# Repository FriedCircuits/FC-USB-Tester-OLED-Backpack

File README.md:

FC-USB-Tester-OLED-Backpack
===========================
This is the source code for the USB Tester OLED Backpack 

Which can be found at:
https://friedcircuits.us/tools/46

To compile this code you will need the following libraries:
===========================
Old Version

[Adafruit GFX](https://github.com/adafruit/Adafruit-GFX-Library)

[Adafruit SSD1306](https://github.com/adafruit/Adafruit_SSD1306)

2.0

Needs [UG8LIB] (https://github.com/olikraus/u8glib)

Both Versions

[TimerOne](https://github.com/PaulStoffregen/TimerOne)

[ClickButton](http://code.google.com/p/clickbutton/)

[Adafruit INA219](https://github.com/adafruit/Adafruit_INA219)

Download ZIP in each version folder for a working set with libraries and configuration of hardware SPI and display size

Use the new firmware version with the new Java app

https://github.com/FriedCircuits/FC-USB-Tester-Data-Logger-App

There may be a bug that shifts the display. We are working on a solution - Testing a new library for the display.

How to update firmware:

http://friedcircuits.us/docs/oled-backpack-how-to-update-firmware/

License: All source code and designs are released under 

Creative Commons NonCommercial-ShareAlike 

CC BY-NC-SA

Please contact me for commercial opportunities.

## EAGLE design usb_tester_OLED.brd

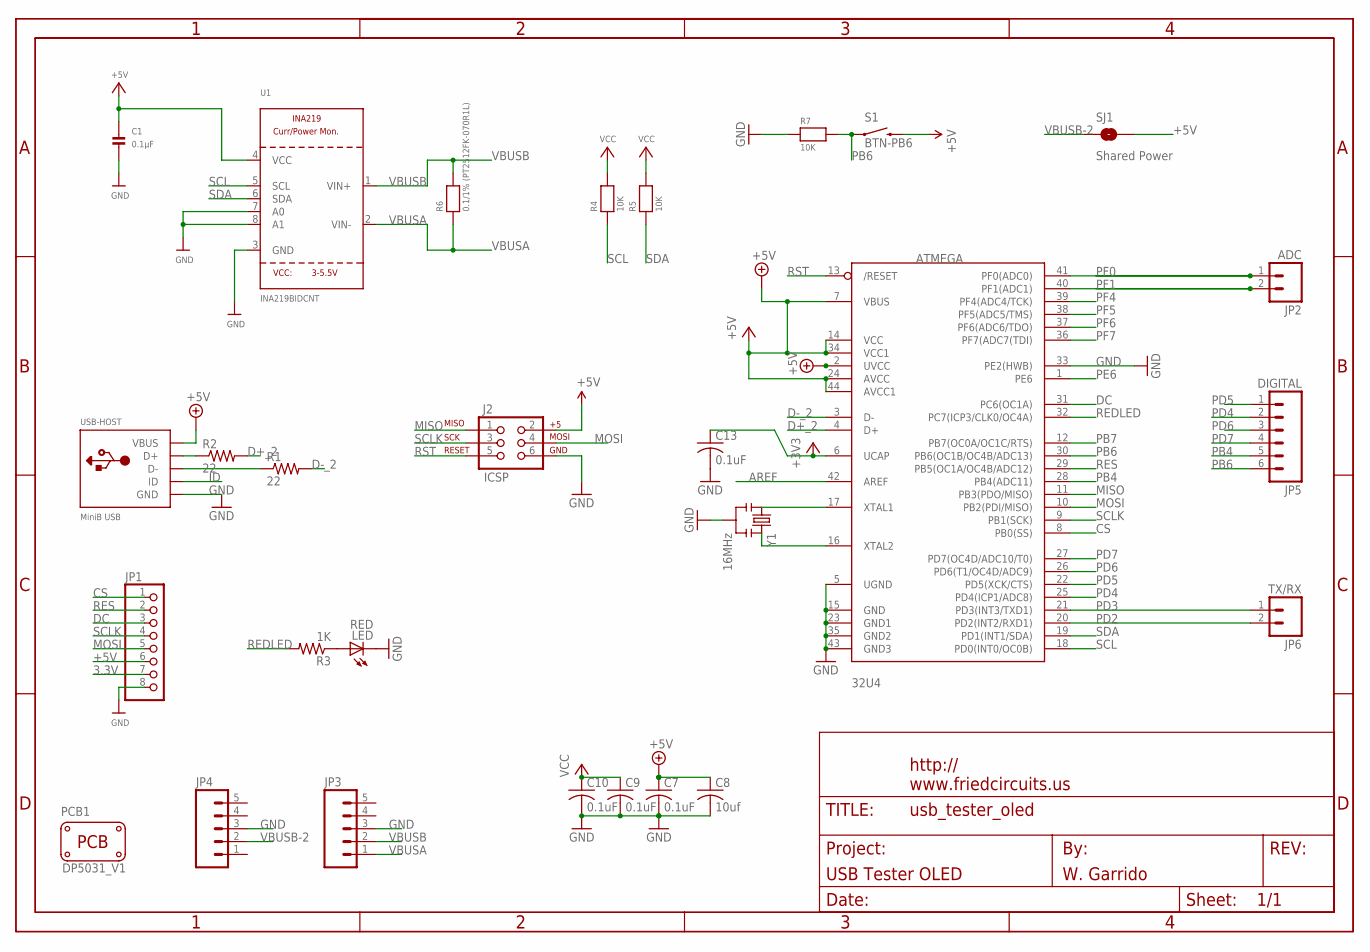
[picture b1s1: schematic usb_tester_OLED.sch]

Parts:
32U4: ATMEGA; TQFP44
C1: 0.1µF; 0805
C7, C9, C10, C13: 0.1uF; C0805K
C8: 10uf; C0805K
J2: ICSP; 2X3_LOCK
JP1: HEADER-1X876MIL; 1X08_ROUND_76
JP2: ADC; 1X02_LOCK
JP3, JP4: M05LOCK; 1X05_LOCK
JP5: DIGITAL; 1X06_LOCK
JP6: TX/RX; 1X02_LOCK
LED: RED; CHIPLED_0805
PCB1: PCB_DP_RECTANGLE-31X50; DP5031_V1
R1, R2: 22; R0805
R3: 1K; R0805
R4, R5, R7: 10K; 0805
R6: 0.1/1% (PT2512FK-070R1L); 2512
S1: BTN-PB6; TACTILE_SWITCH_SMD
SJ1: Shared Power; SJ_2S-TRACE
U1: INA219BIDCNT; SOT23-8
U$1: FRAME_DINA4_L; FC_CREDIT
USB-HOST: MiniB USB; USB-MINIB
Y1: 16MHz; RESONATOR-SMD

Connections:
3.3V: JP1.7
+3V3: 32U4.6 (UCAP), C13.1
+5V: 32U4.2 (UVCC), 32U4.7 (VBUS), 32U4.14 (VCC), 32U4.24 (AVCC), 32U4.34 (VCC1), 32U4.44 (AVCC1), C1.1, C7.1, C8.1, C9.1, C10.1, J2.2, JP1.6, R4.2, R5.2, S1.3 (2), SJ1.2, U1.4 (VCC), USB-HOST.VBUS
AREF: 32U4.42 (AREF)
CS: 32U4.8 (PB0(SS)), JP1.1
D+_2: 32U4.4 (D+), R2.2
D-_2: 32U4.3 (D-), R1.2
DC: 32U4.31 (PC6(OC1A)), JP1.3
GND: 32U4.5 (UGND), 32U4.15 (GND), 32U4.23 (GND1), 32U4.33 (PE2(HWB)), 32U4.35 (GND2), 32U4.43 (GND3), C1.2, C7.2, C8.2, C9.2, C10.2, C13.2, J2.6, JP1.8, JP3.3, JP4.3, LED.C, R7.1, U1.3 (GND), U1.7 (A0), U1.8 (A1), USB-HOST.GND, Y1.2
ID: USB-HOST.ID
MISO: 32U4.11 (PB3(PDO/MISO)), J2.1
MOSI: 32U4.10 (PB2(PDI/MISO)), J2.4, JP1.5
unnamed: LED.A, R3.1
unnamed: R2.1, USB-HOST.D+
unnamed: R1.1, USB-HOST.D-
unnamed: 32U4.17 (XTAL1), Y1.1
unnamed: 32U4.16 (XTAL2), Y1.3
PB4: 32U4.28 (PB4(ADC11)), JP5.5
PB6: 32U4.30 (PB6(OC1B/OC4B/ADC13)), JP5.6, R7.2, S1.1
PB7: 32U4.12 (PB7(OC0A/OC1C/RTS))
PD2: 32U4.20 (PD2(INT2/RXD1)), JP6.2
PD3: 32U4.21 (PD3(INT3/TXD1)), JP6.1
PD4: 32U4.25 (PD4(ICP1/ADC8)), JP5.2
PD5: 32U4.22 (PD5(XCK/CTS)), JP5.1
PD6: 32U4.26 (PD6(T1/OC4D/ADC9)), JP5.3
PD7: 32U4.27 (PD7(OC4D/ADC10/T0)), JP5.4
PE6: 32U4.1 (PE6)
PF0: 32U4.41 (PF0(ADC0)), JP2.1
PF1: 32U4.40 (PF1(ADC1)), JP2.2
PF4: 32U4.39 (PF4(ADC4/TCK))
PF5: 32U4.38 (PF5(ADC5/TMS))
PF6: 32U4.37 (PF6(ADC6/TDO))
PF7: 32U4.36 (PF7(ADC7(TDI))
REDLED: 32U4.32 (PC7(ICP3/CLK0/OC4A)), R3.2
RES: 32U4.29 (PB5(OC1A/OC4B/ADC12)), JP1.2
RST: 32U4.13 (/RESET), J2.5
SCL: 32U4.18 (PD0(INT0/OC0B)), R4.1, U1.5 (SCL)
SCLK: 32U4.9 (PB1(SCK)), J2.3, JP1.4
SDA: 32U4.19 (PD1(INT1/SDA)), R5.1, U1.6 (SDA)
VBUSA: JP3.1, R6.1, U1.2 (VIN-)
VBUSB: JP3.2, R6.2, U1.1 (VIN+)
VBUSB-2: JP4.2, SJ1.1

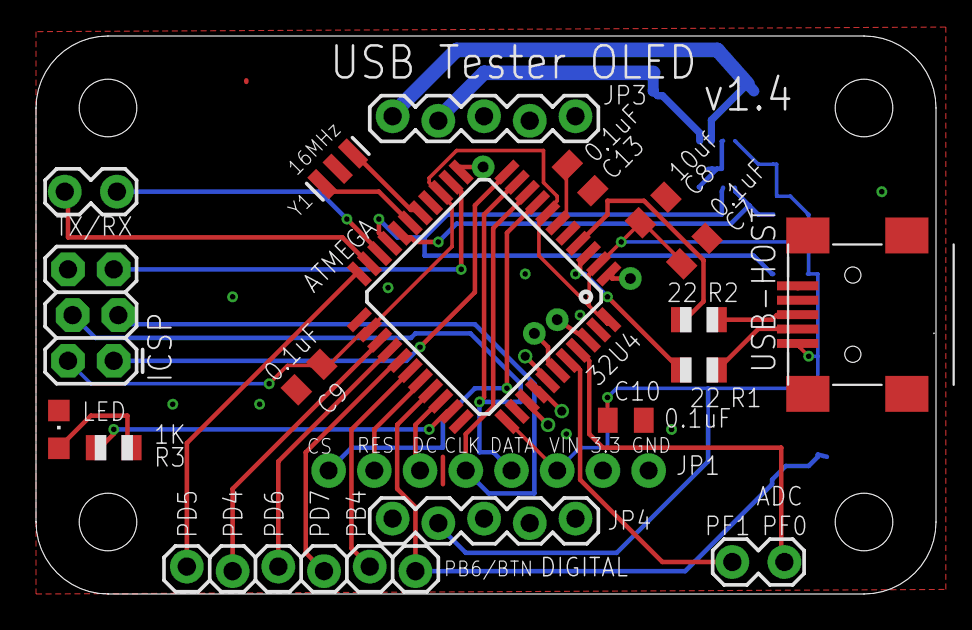
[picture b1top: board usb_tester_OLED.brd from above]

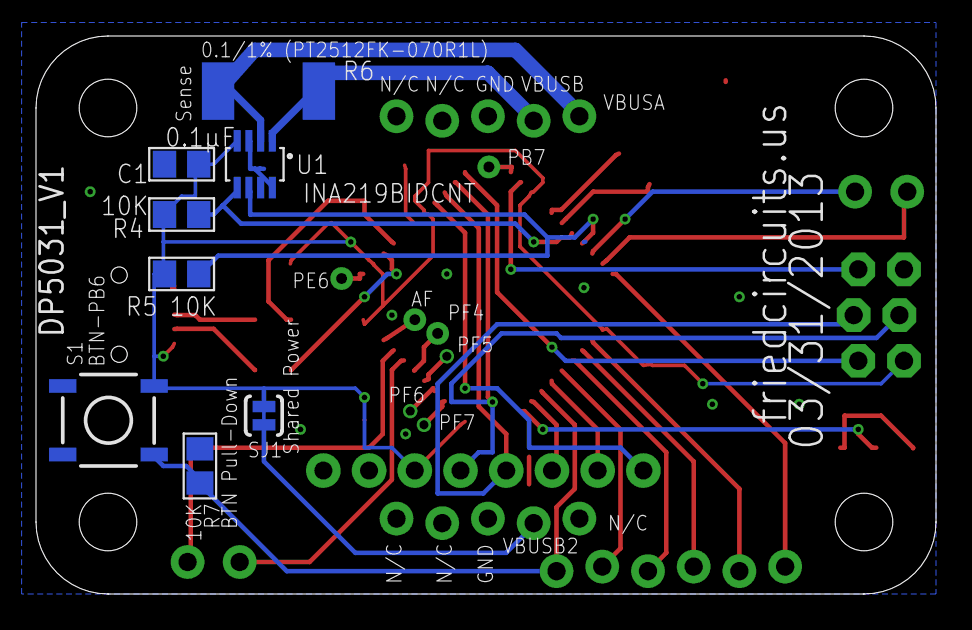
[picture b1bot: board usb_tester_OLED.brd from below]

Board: 2 copper layers, 50.0 x 31.0 mm, 29 parts (8 on the bottom side), 33 nets.

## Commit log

2013-02-12 Added decription and needed libraries
2013-02-12 Formatting
2013-02-12 Revert "Initial Commit"
    This reverts commit 4cfcb35430fffdd77c245b26491d4ba563c6f1f5.
2013-02-12 Added link to Java App.
2013-02-12 Formating
2013-03-13 Updated license
2013-04-12 Add autoscroll for the graph
    And move the directory to an Arduino-friendly name
2013-04-22 Uncommented filter for no load
2013-04-22 Typo in comment
2013-04-23 Added design files in Eagle and PNG
2013-04-27 Fixed no load filter
2013-04-28 Make value graph scroll and not cycle.
2013-08-26 Redesigned display
    -Removed SVolt and BVolt
    -Moved Current\Volt under graph
    -Extend graph width of display
    -Use clearDisplay to speed up redraws
    -Reduce logo display time
    -Enabled button to cycle display speed
2013-08-26 Fixed URL
2013-08-27 Add autoscale
    Display is now able to autoscale. By default there are a few values
    defined (0.2, 0.5, 1, 1.5 and 2 A) but you can adjust these by just
    changing the array.
    The drawing routine is now less efficient time-wise, since I now use
    the previous values buffer with the read reading, and scale it to
    24-0 at draw time. The reason for this, is that when scaling down,
2013-08-28 Zip with fully working versions of libraries.
    Extract to Arduino folder.
2013-08-28 Updated with auto scale version
2013-08-29 Lots of new features: - Now logs energy (mWh and mAh) - Multiple screens (use button to cycle)
    Displays: min Voltage, max current, mWh, mAh, peak power, along
    with relevant values at each of those points (current at min voltage,
    voltage at max current, current and voltage at peak power, etc).
    Serial output is unchanged for now, but I'll probably update this
    next.
2013-08-31 One more screen in big characters
    Also now rounds the display of some readings to make screens
    more legible.
2013-09-08 Cleanups and add a "big reading" Voltage & Current screen
2013-09-08 Forgot a "break" statement earlier...
2013-09-08 Fix a few typos
2013-09-10 Update decimal handing for mA
    -Added decimal to lower display
    -Top display auto adjust if decimal needed
    -Turned off debug by default
    -ToDo: Long press clears peaks and energy usage
2013-09-10 Added long button press to clear data
    Long button press about 3-4 seconds
    Clears all peak, min and energy usage data
2013-09-10 Updated README with need TimerOne Library
2013-09-11 Add message display handling function
    Call setMsg(msg, time)
    updated default scales.
2013-09-11 Removed decimal
    Resolution of IC is .8mA
2013-09-11 Fixed min current\voltage reset
2013-09-12 Updated button handling
    Rewrote button function using ClickButton library from
    http://code.google.com/p/clickbutton/wiki/Usage
    Fixes screen changing when reseting,
    so action happens after button is let go
    Added 2nd printJustified function for decimal
    Now mWh and mAh use decimals
2013-09-12 Updated readme with clickbutton library
2013-10-03 Updated working package
2013-10-03 Formatting in readme
2013-12-11 Uploaded version 2 files
2013-12-21 Working ZIP for v2
2014-01-13 Improved analogRead for D-\+
    D-\+ readings are not based on VCC instead of assumed 5v. Also split
    energy readings screen to multiple lines.
2014-06-30 Newest ZIP with JSON support.
2014-07-01 Fixed screen size in library
2014-11-06 Current Firmware version
    For the Java so it can check the current firmware version.
2014-11-09 See changelog
    Cleaned up screens, added bar graphs and firmware version command. Using
    ug8lib.
2014-11-11 Added firmware version to startup info
2014-12-21 Revert "Added firmware version to startup info"
    This reverts commit ae1a7a8cbf1ab4103c57a1c15dbe1268bf3a7579.
2014-12-21 Zip for 2.10
2015-02-08 Compiled Hex
2015-11-13 Added EagleCAD Library for OLED
2015-11-13 Updated readme with new libraries used.
2015-11-13 Updated readme libraries used.
2016-11-12 Beta of new features
    Event Triggers
    New commands
    Saving of settings to EEPROM
    Added documentation using doxygen
2016-11-12 Remove latex
2016-11-12 Moved ino to subdirectory
2016-11-12 Fixed readme list
2016-11-12 Changed EEPROM to updateBlock
2016-11-12 Update TimerOne link in readme
2016-11-12 Added library submodules
2016-11-12 submodules
2016-11-12 Remove mention of zip, using linked libraries instead
2016-11-12 Include click library from google code
    https://code.google.com/archive/p/clickbutton/
2016-11-12 Include U8glib
2016-11-12 Rewording
2016-11-12 Added INA219 lib
2016-11-13 Added note to skip config load on boot
2016-11-13 Added run time in features
2016-11-13 Added hex with bootloader
2017-02-09 Speed up i2c
    Also fixes averging output on serial showing 0
2017-02-22 Beta Firmware 2.3 Release - 1kHz sample speed
    1kHz sample speed + optimizations
2017-02-22 Beta Firmware 2.3 Release - 1kHz sample speed
    1kHz sample speed + optimizations
    Updated readme
2017-03-04 Fix for mAh/mWh
    Was displaying .00 instead of the value for mAh/mWh
2017-03-04 Added sketch
    Forgot to upload sketch.
2017-03-05 Fixed reset of mAh/mWh Issue #9
2017-03-06 Fixed mAh/mWh calculation issue #8
2017-03-20 optimize mAh/mWh
2018-11-22 Add PDFs of board and schematic

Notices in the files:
parts and their libraries:
SparkFun-Connectors: Licensing: CC v3.0 Share-Alike You are welcome to use this library for commercial purposes.
